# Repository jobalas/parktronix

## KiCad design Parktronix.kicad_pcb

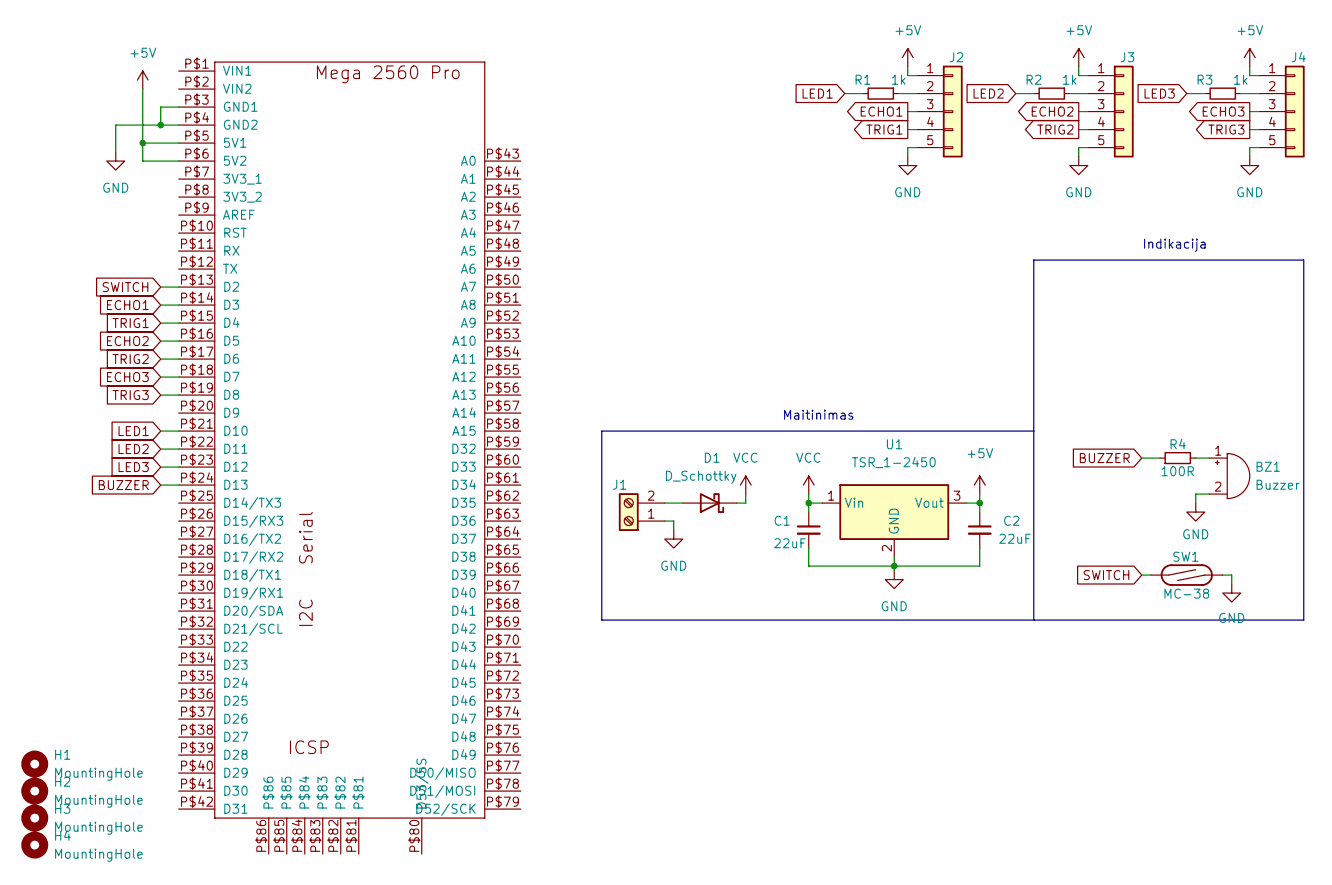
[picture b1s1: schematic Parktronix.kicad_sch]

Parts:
111: MEGAPROMINI
BZ1: Buzzer; Buzzer_TDK_PS1240P02BT_D12.2mm_H6.5mm
C1, C2: 22uF; CP_Elec_5x5.8
D1: D_Schottky; D_5W_P12.70mm_Horizontal
H1, H2, H3, H4: MountingHole; MountingHole_3.2mm_M3
J1: Screw_Terminal_01x02; TerminalBlock_Phoenix_MKDS-1,5-2_1x02_P5.00mm_Horizontal
J2, J3, J4: Conn_01x05; PinHeader_1x05_P2.54mm_Vertical
R1, R2, R3: 1k; R_Axial_DIN0207_L6.3mm_D2.5mm_P10.16mm_Horizontal
R4: 100R; R_Axial_DIN0207_L6.3mm_D2.5mm_P10.16mm_Horizontal
SW1: MC-38; TerminalBlock_Phoenix_MKDS-1,5-2_1x02_P5.00mm_Horizontal
U1: TSR_1-2450; Converter_DCDC_TRACO_TSR-1_THT

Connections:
+5V: 111.P$5 (5V1), 111.P$6 (5V2), C2.1, J2.1, J3.1, J4.1, U1.3 (Vout)
BUZZER: 111.P$24 (D13), R4.1
ECHO1: 111.P$14 (D3), J2.3
ECHO2: 111.P$16 (D5), J3.3
ECHO3: 111.P$18 (D7), J4.3
GND: 111.P$3 (GND1), 111.P$4 (GND2), BZ1.2 (+), C1.2, C2.2, J1.1, J2.5, J3.5, J4.5, SW1.2, U1.2 (GND)
LED1: 111.P$21 (D10), R1.2
LED2: 111.P$22 (D11), R2.2
LED3: 111.P$23 (D12), R3.2
unnamed: BZ1.1 (-), R4.2
unnamed: D1.2 (A), J1.2
unnamed: J3.2, R2.1
unnamed: J4.2, R3.1
unnamed: J2.2, R1.1
SWITCH: 111.P$13 (D2), SW1.1
TRIG1: 111.P$15 (D4), J2.4
TRIG2: 111.P$17 (D6), J3.4
TRIG3: 111.P$19 (D8), J4.4
VCC: C1.1, D1.1 (K), U1.1 (Vin)

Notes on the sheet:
Maitinimas
Indikacija

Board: 2 copper layers, 19 parts (0 on the bottom side), 19 nets, no tracks yet.

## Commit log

2022-03-15 uploading everything to git
